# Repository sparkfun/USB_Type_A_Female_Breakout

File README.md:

Breakout Board for USB A Female
===============================

[*USB Type A Female Breakout Board (BOB-12700)*](https://www.sparkfun.com/products/12700)

USB breakout board for a Type A connector.

This part was created in Eagle v6.5.0. Example sketches were created in Arduino v1.0.5.

Repository Contents
-------------------

* **/Fritzing** - Source files and examples for Fritzing diagrams
* **/Hardware** - All Eagle design files (.brd, .sch)
* **/Production** - Test bed files and production panel files

Documentation
--------------
* **[Hookup Guide](https://learn.sparkfun.com/tutorials/usb-type-a-female-breakout-hookup-guide)** - Basic hookup guide.

Version History
---------------
* **v1.0** Initial release

License Information
-------------------
The hardware is released under [Creative Commons ShareAlike 4.0 International](https://creativecommons.org/licenses/by-sa/4.0/).
The code is beerware; if you see me (or any other SparkFun employee) at the local, and you've found our code helpful, please buy us a round!

Distributed as-is; no warranty is given.

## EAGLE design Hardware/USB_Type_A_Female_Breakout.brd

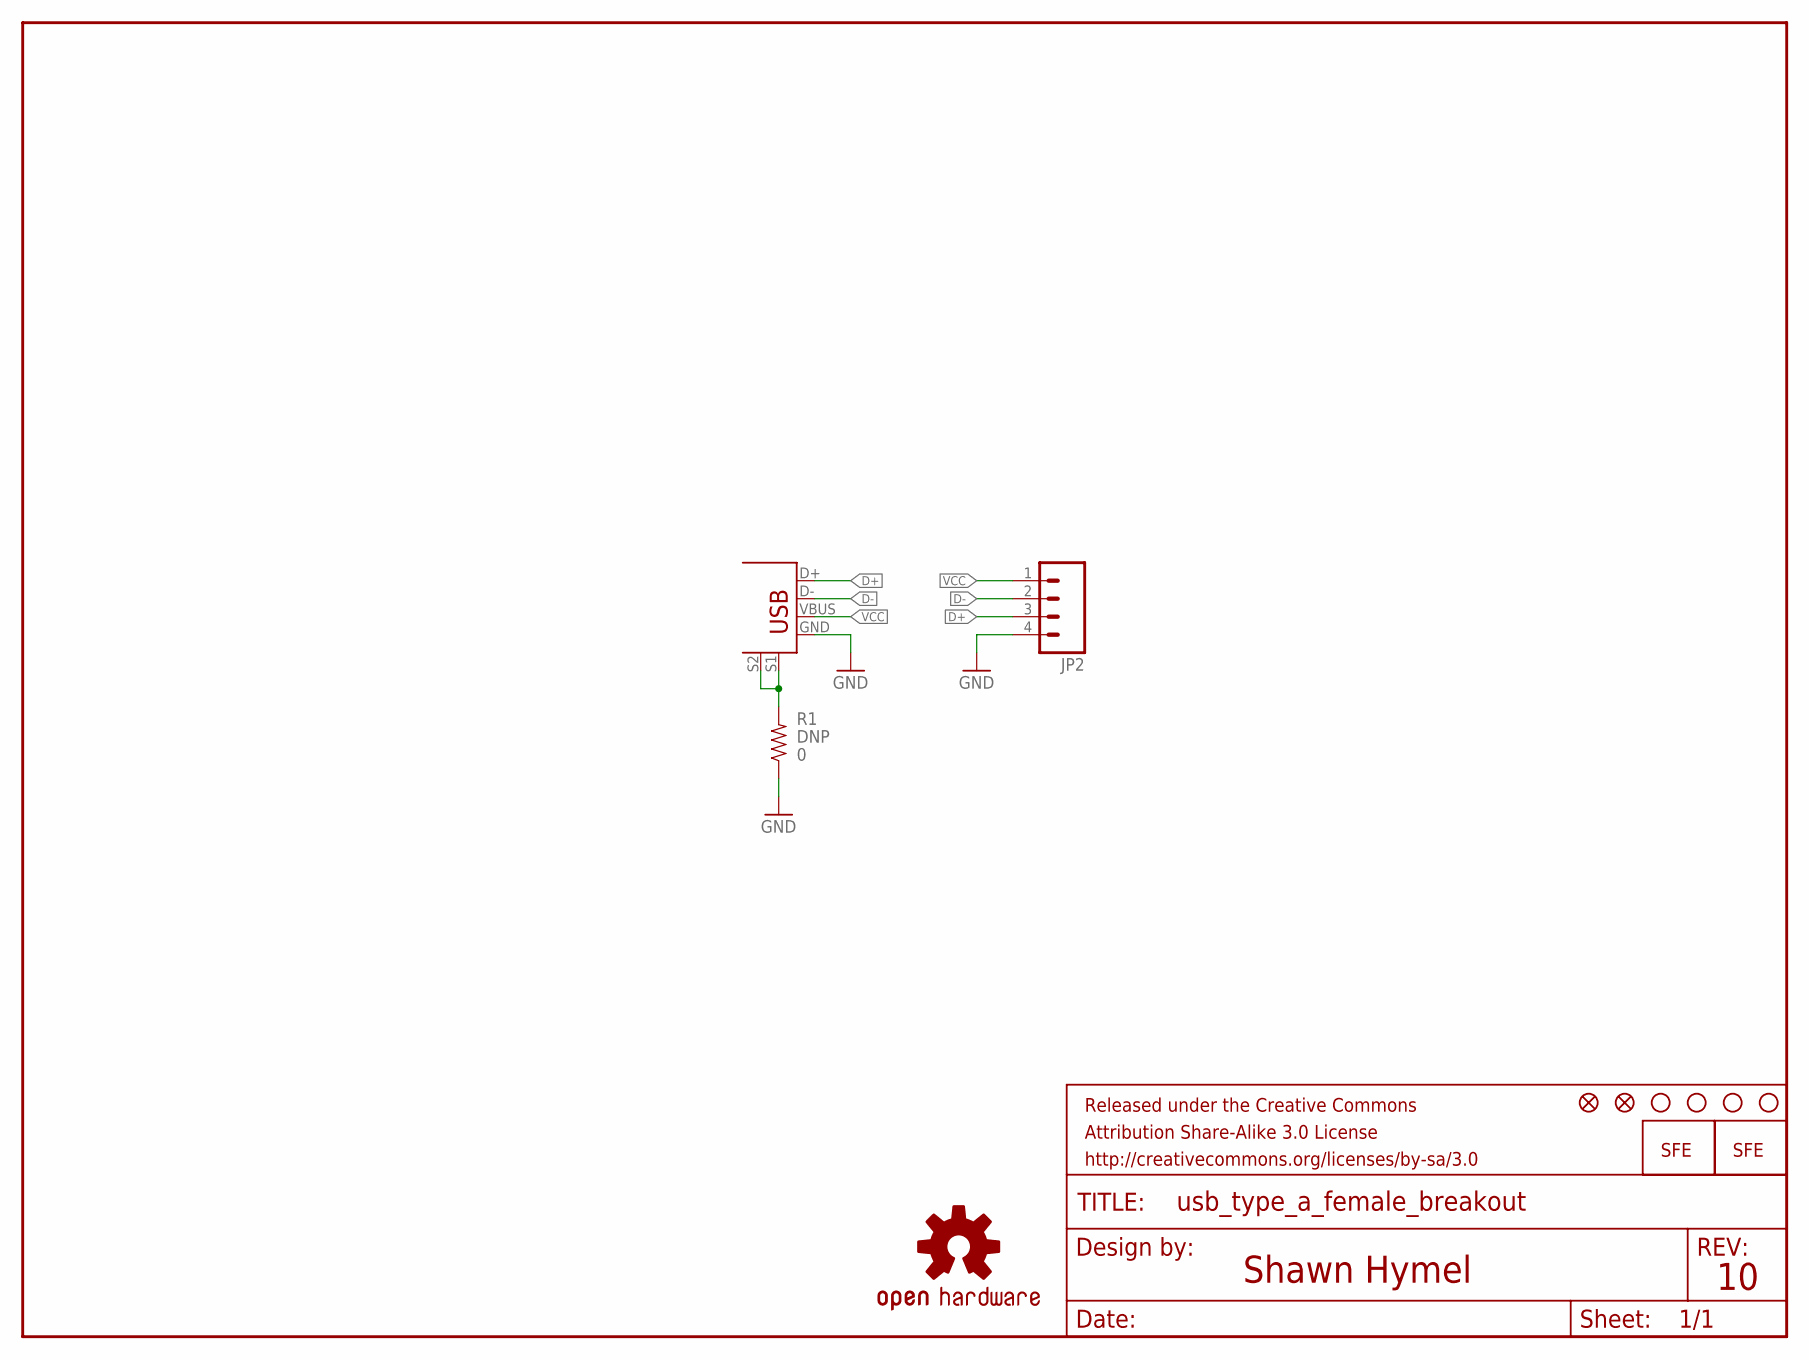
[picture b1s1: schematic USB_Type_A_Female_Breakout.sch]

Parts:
FID1, FID2: FIDUCIAL1X2; FIDUCIAL-1X2
FRAME1: FRAME-LETTER; CREATIVE_COMMONS
JP1: USB+SHIELDUSB-A-S-NOSILK-FEMALE; USB-A-S-NOSILK-FEMALE
JP2: M04PTH; 1X04
LOGO1: LOGO-SFENEW; SFE-NEW-WEBLOGO
LOGO2: OSHW-LOGOS; OSHW-LOGO-S
LOGO3: LOGO-SFESK; SFE-LOGO-FLAME
R1: 0; 0603-RES
STANDOFF1, STANDOFF2, STANDOFF3, STANDOFF4: STAND-OFF

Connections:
D+: JP1.D+, JP2.3
D-: JP1.D-, JP2.2
GND: JP1.GND, JP2.4, R1.1
unnamed: JP1.S1, JP1.S2, R1.2
VCC: JP1.VBUS, JP2.1

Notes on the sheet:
Shawn Hymel

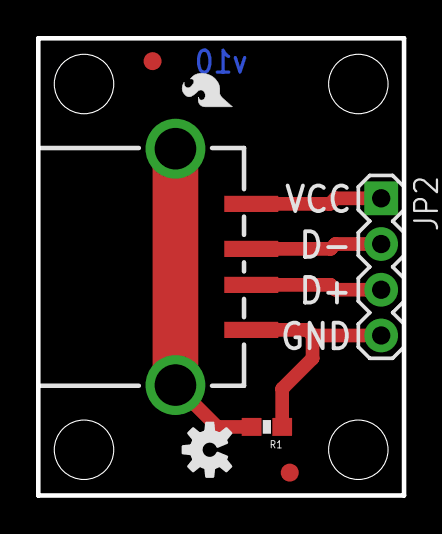
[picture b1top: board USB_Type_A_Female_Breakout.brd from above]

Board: 2 copper layers, 20.3 x 25.4 mm, 13 parts (1 on the bottom side), 5 nets.

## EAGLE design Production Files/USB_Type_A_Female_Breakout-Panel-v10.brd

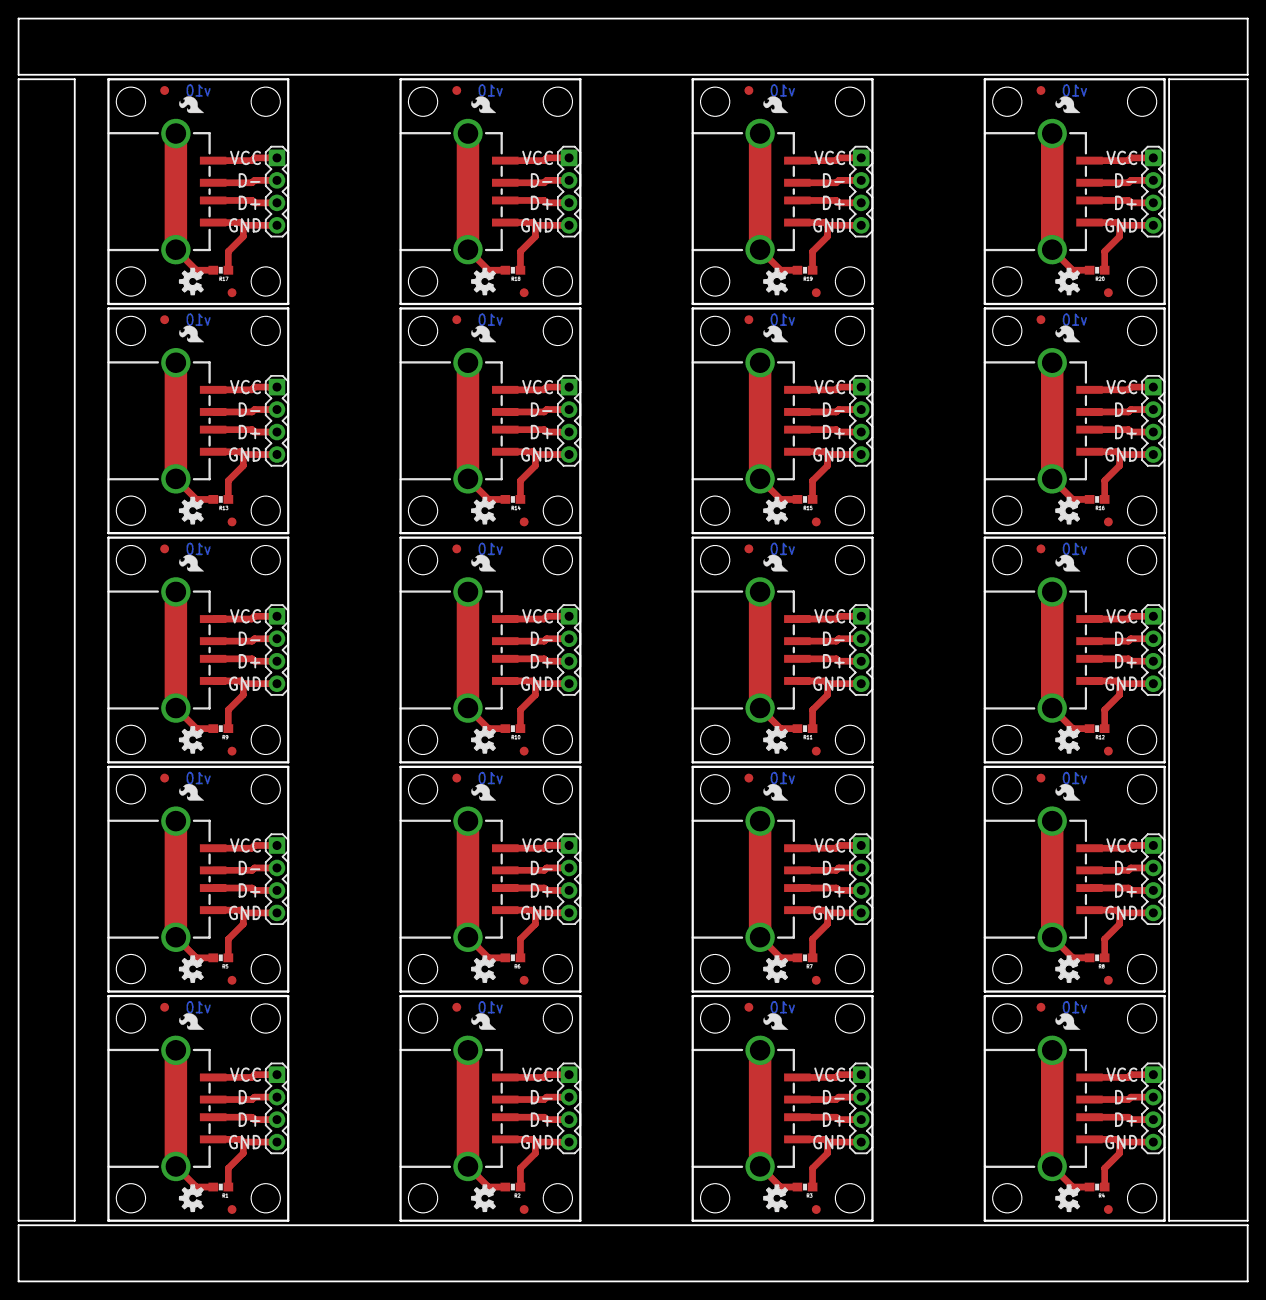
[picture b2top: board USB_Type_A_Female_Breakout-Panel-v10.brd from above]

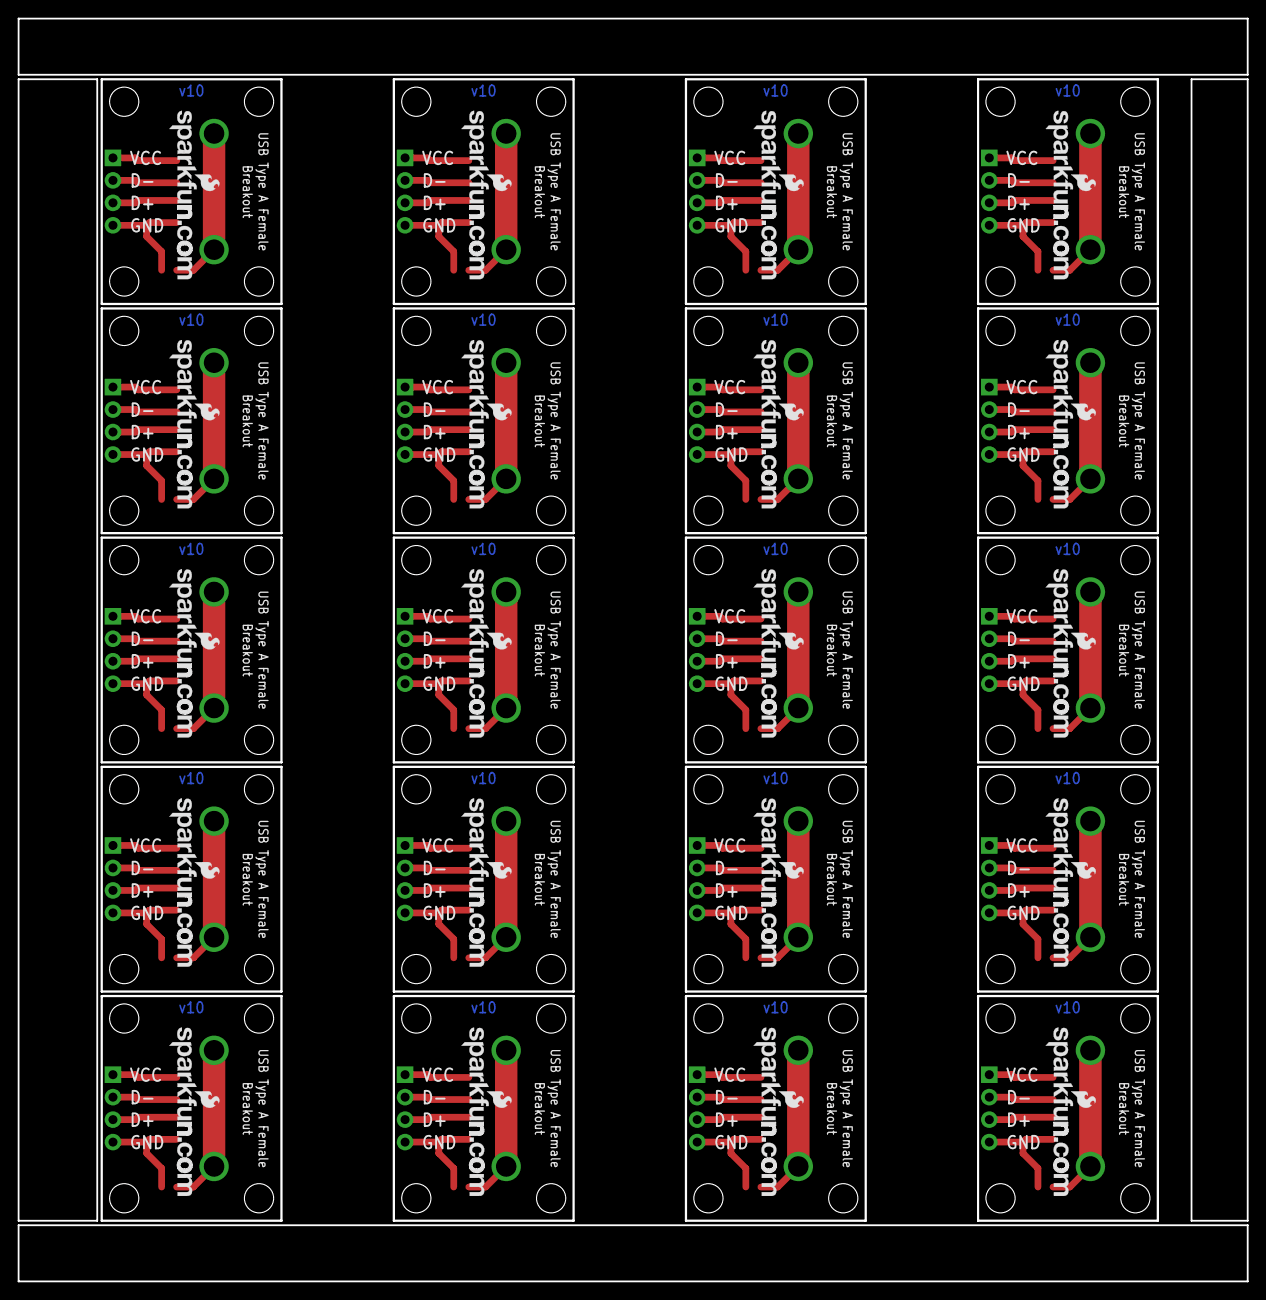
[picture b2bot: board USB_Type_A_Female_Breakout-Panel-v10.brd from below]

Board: 2 copper layers, 138.9 x 142.7 mm, 240 parts (20 on the bottom side), 100 nets.

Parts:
FID1, FID2, FID3, FID4, FID5, FID6, FID7, FID8, FID9, FID10, FID11, FID12, FID13, FID14, FID15, FID16, FID17, FID18, FID19, FID20, FID21, FID22, FID23, FID24, FID25, FID26, FID27, FID28, FID29, FID30, FID31, FID32, FID33, FID34, FID35, FID36, FID37, FID38, FID39, FID40: FIDUCIAL1X2; FIDUCIAL-1X2
JP1, JP3, JP5, JP7, JP9, JP11, JP13, JP15, JP17, JP19, JP21, JP23, JP25, JP27, JP29, JP31, JP33, JP35, JP37, JP39: USB+SHIELDUSB-A-S-NOSILK-FEMALE; USB-A-S-NOSILK-FEMALE
JP2, JP4, JP6, JP8, JP10, JP12, JP14, JP16, JP18, JP20, JP22, JP24, JP26, JP28, JP30, JP32, JP34, JP36, JP38, JP40: 1X04
LOGO1, LOGO4, LOGO7, LOGO10, LOGO13, LOGO16, LOGO19, LOGO22, LOGO25, LOGO28, LOGO31, LOGO34, LOGO37, LOGO40, LOGO43, LOGO46, LOGO49, LOGO52, LOGO55, LOGO58: LOGO-SFENEW; SFE-NEW-WEBLOGO
LOGO2, LOGO5, LOGO8, LOGO11, LOGO14, LOGO17, LOGO20, LOGO23, LOGO26, LOGO29, LOGO32, LOGO35, LOGO38, LOGO41, LOGO44, LOGO47, LOGO50, LOGO53, LOGO56, LOGO59: OSHW-LOGOS; OSHW-LOGO-S
LOGO3, LOGO6, LOGO9, LOGO12, LOGO15, LOGO18, LOGO21, LOGO24, LOGO27, LOGO30, LOGO33, LOGO36, LOGO39, LOGO42, LOGO45, LOGO48, LOGO51, LOGO54, LOGO57, LOGO60: LOGO-SFESK; SFE-LOGO-FLAME
R1, R2, R3, R4, R5, R6, R7, R8, R9, R10, R11, R12, R13, R14, R15, R16, R17, R18, R19, R20: 0; 0603-RES
STANDOFF1, STANDOFF2, STANDOFF3, STANDOFF4, STANDOFF5, STANDOFF6, STANDOFF7, STANDOFF8, STANDOFF9, STANDOFF10, STANDOFF11, STANDOFF12, STANDOFF13, STANDOFF14, STANDOFF15, STANDOFF16, STANDOFF17, STANDOFF18, STANDOFF19, STANDOFF20, STANDOFF21, STANDOFF22, STANDOFF23, STANDOFF24, STANDOFF25, STANDOFF26, STANDOFF27, STANDOFF28, STANDOFF29, STANDOFF30, STANDOFF31, STANDOFF32, STANDOFF33, STANDOFF34, STANDOFF35, STANDOFF36, STANDOFF37, STANDOFF38, STANDOFF39, STANDOFF40, STANDOFF41, STANDOFF42, STANDOFF43, STANDOFF44, STANDOFF45, STANDOFF46, STANDOFF47, STANDOFF48, STANDOFF49, STANDOFF50, STANDOFF51, STANDOFF52, STANDOFF53, STANDOFF54, STANDOFF55, STANDOFF56, STANDOFF57, STANDOFF58, STANDOFF59, STANDOFF60, STANDOFF61, STANDOFF62, STANDOFF63, STANDOFF64, STANDOFF65, STANDOFF66, STANDOFF67, STANDOFF68, STANDOFF69, STANDOFF70, STANDOFF71, STANDOFF72, STANDOFF73, STANDOFF74, STANDOFF75, STANDOFF76, STANDOFF77, STANDOFF78, STANDOFF79, STANDOFF80: STAND-OFF

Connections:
D+: JP1.D+, JP2.3
D+1: JP3.D+, JP4.3
D+2: JP5.D+, JP6.3
D+3: JP7.D+, JP8.3
D+4: JP9.D+, JP10.3
D+5: JP11.D+, JP12.3
D+6: JP13.D+, JP14.3
D+7: JP15.D+, JP16.3
D+8: JP17.D+, JP18.3
D+9: JP19.D+, JP20.3
D+10: JP21.D+, JP22.3
D+11: JP23.D+, JP24.3
D+12: JP25.D+, JP26.3
D+13: JP27.D+, JP28.3
D+14: JP29.D+, JP30.3
D+15: JP31.D+, JP32.3
D+16: JP33.D+, JP34.3
D+17: JP35.D+, JP36.3
D+18: JP37.D+, JP38.3
D+19: JP39.D+, JP40.3
D-: JP1.D-, JP2.2
D-1: JP3.D-, JP4.2
D-2: JP5.D-, JP6.2
D-3: JP7.D-, JP8.2
D-4: JP9.D-, JP10.2
D-5: JP11.D-, JP12.2
D-6: JP13.D-, JP14.2
D-7: JP15.D-, JP16.2
D-8: JP17.D-, JP18.2
D-9: JP19.D-, JP20.2
D-10: JP21.D-, JP22.2
D-11: JP23.D-, JP24.2
D-12: JP25.D-, JP26.2
D-13: JP27.D-, JP28.2
D-14: JP29.D-, JP30.2
D-15: JP31.D-, JP32.2
D-16: JP33.D-, JP34.2
D-17: JP35.D-, JP36.2
D-18: JP37.D-, JP38.2
D-19: JP39.D-, JP40.2
GND: JP1.GND, JP2.4, R1.1
GND1: JP3.GND, JP4.4, R2.1
GND2: JP5.GND, JP6.4, R3.1
GND3: JP7.GND, JP8.4, R4.1
GND4: JP9.GND, JP10.4, R5.1
GND5: JP11.GND, JP12.4, R6.1
GND6: JP13.GND, JP14.4, R7.1
GND7: JP15.GND, JP16.4, R8.1
GND8: JP17.GND, JP18.4, R9.1
GND9: JP19.GND, JP20.4, R10.1
GND10: JP21.GND, JP22.4, R11.1
GND11: JP23.GND, JP24.4, R12.1
GND12: JP25.GND, JP26.4, R13.1
GND13: JP27.GND, JP28.4, R14.1
GND14: JP29.GND, JP30.4, R15.1
GND15: JP31.GND, JP32.4, R16.1
GND16: JP33.GND, JP34.4, R17.1
GND17: JP35.GND, JP36.4, R18.1
GND18: JP37.GND, JP38.4, R19.1
GND19: JP39.GND, JP40.4, R20.1
unnamed: JP1.S1, JP1.S2, R1.2
unnamed: JP3.S1, JP3.S2, R2.2
unnamed: JP5.S1, JP5.S2, R3.2
unnamed: JP7.S1, JP7.S2, R4.2
unnamed: JP9.S1, JP9.S2, R5.2
unnamed: JP11.S1, JP11.S2, R6.2
unnamed: JP13.S1, JP13.S2, R7.2
unnamed: JP15.S1, JP15.S2, R8.2
unnamed: JP17.S1, JP17.S2, R9.2
unnamed: JP19.S1, JP19.S2, R10.2
unnamed: JP21.S1, JP21.S2, R11.2
unnamed: JP23.S1, JP23.S2, R12.2
unnamed: JP25.S1, JP25.S2, R13.2
unnamed: JP27.S1, JP27.S2, R14.2
unnamed: JP29.S1, JP29.S2, R15.2
unnamed: JP31.S1, JP31.S2, R16.2
unnamed: JP33.S1, JP33.S2, R17.2
unnamed: JP35.S1, JP35.S2, R18.2
unnamed: JP37.S1, JP37.S2, R19.2
unnamed: JP39.S1, JP39.S2, R20.2
VCC: JP1.VBUS, JP2.1
VCC1: JP3.VBUS, JP4.1
VCC2: JP5.VBUS, JP6.1
VCC3: JP7.VBUS, JP8.1
VCC4: JP9.VBUS, JP10.1
VCC5: JP11.VBUS, JP12.1
VCC6: JP13.VBUS, JP14.1
VCC7: JP15.VBUS, JP16.1
VCC8: JP17.VBUS, JP18.1
VCC9: JP19.VBUS, JP20.1
VCC10: JP21.VBUS, JP22.1
VCC11: JP23.VBUS, JP24.1
VCC12: JP25.VBUS, JP26.1
VCC13: JP27.VBUS, JP28.1
VCC14: JP29.VBUS, JP30.1
VCC15: JP31.VBUS, JP32.1
VCC16: JP33.VBUS, JP34.1
VCC17: JP35.VBUS, JP36.1
VCC18: JP37.VBUS, JP38.1
VCC19: JP39.VBUS, JP40.1

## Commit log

2013-12-05 Copied in templates for .gitignore and License
2013-12-05 Created schematic and layout
2013-12-09 Renamed schematic and layout files
2013-12-30 Moved USB jack back. Added 0 Ohm DNP resistor to optionally connect USB jack shield to GND.
2014-01-02 Created Panel
    v10
2014-02-04 Added pdf of schematic
2014-02-05 Added README information to all directories
2014-02-05 Fixed product image and link on README
2014-02-05 That didn't work. Let's try again. Trying to fix README image...
2014-02-05 Better. Centering README photo
2014-02-05 No, seriously, really centering the photo in the README this time
2014-02-05 Nevermind, can't center stuff in GitHub markdown. Just gonna left-align the image
2014-02-06 Added Fritzing diagrams
2014-02-13 Updating README license
2014-09-10 re-did panel v10
2018-12-06 Rename LICENSE to LICENSE.md
2023-09-15 Add Board Dimensions
2025-06-27 Update README.md
    Updating link

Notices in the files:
parts and their libraries:
SparkFun-Aesthetics: Licensing: CC v3.0 Share-Alike You are welcome to use this library for commercial purposes.
SparkFun-Aesthetics: Released under the Creative Commons Attribution Share-Alike 3.0 License
SparkFun-Aesthetics: http://creativecommons.org/licenses/by-sa/3.0
